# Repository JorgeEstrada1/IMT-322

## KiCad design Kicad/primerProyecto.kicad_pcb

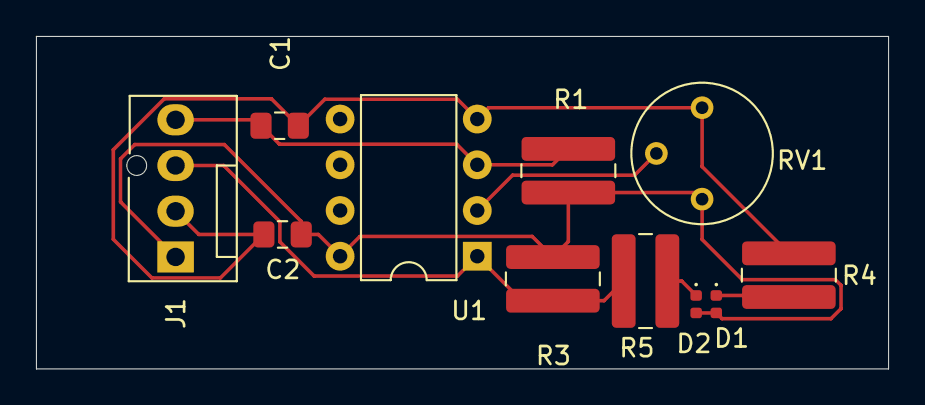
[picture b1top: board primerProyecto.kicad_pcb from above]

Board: 2 copper layers, 47.3 x 18.5 mm, 11 parts (0 on the bottom side), 7 nets.

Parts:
C1, C2: 1uF; C_0805_2012Metric_Pad1.18x1.45mm_HandSolder
D1, D2: LED; LED_0402_1005Metric
J1: Conn_01x04; FanPinHeader_1x04_P2.54mm_Vertical
R1, R3: 10K; R_1020_2550Metric_Pad1.33x5.20mm_HandSolder
R4, R5: 1K; R_1020_2550Metric_Pad1.33x5.20mm_HandSolder
RV1: Poten 10K; Potentiometer_Bourns_3339P_Vertical
U1: LM393; DIP-8_W7.62mm

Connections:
/AC: C1.1, J1.4, R1.2, U1.3 (+)
/OUT: J1.3, R3.2, R5.2, U1.1
GND: C1.2, C2.2, J1.2, R4.2, RV1.3, U1.4 (V-)
unnamed: D1.1 (K), R4.1
unnamed: D2.1 (K), R5.1
unnamed: RV1.2, U1.2 (-)
VCC: C2.1, D1.2 (A), D2.2 (A), J1.1, R1.1, R3.1, RV1.1, U1.8 (V+)

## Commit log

2024-02-17 Hola
2024-02-17 Blink
2024-02-24 Ejercicio Punto 1 Leds
2024-02-24 PUNTO_2
2024-03-02 Practica2
2024-03-02 Punto2
2024-03-09 practica3
2024-03-19 Examen En parejas 19/3
2024-03-19 Punto1
2024-03-19 Examen
2024-03-19 ProyectoFinal
2024-03-19 UltimoPuntoPractica2
2024-03-19 Practica3UltimoPunto
2024-04-06 Primera PCB kiCAD
2024-04-21 practica en clase
2024-04-22 Modulo Lm2596
2024-04-25 Asensor
2024-04-27 Examen 2
2024-05-21 Blink raspberry
2025-04-21 Se creó con Colab
